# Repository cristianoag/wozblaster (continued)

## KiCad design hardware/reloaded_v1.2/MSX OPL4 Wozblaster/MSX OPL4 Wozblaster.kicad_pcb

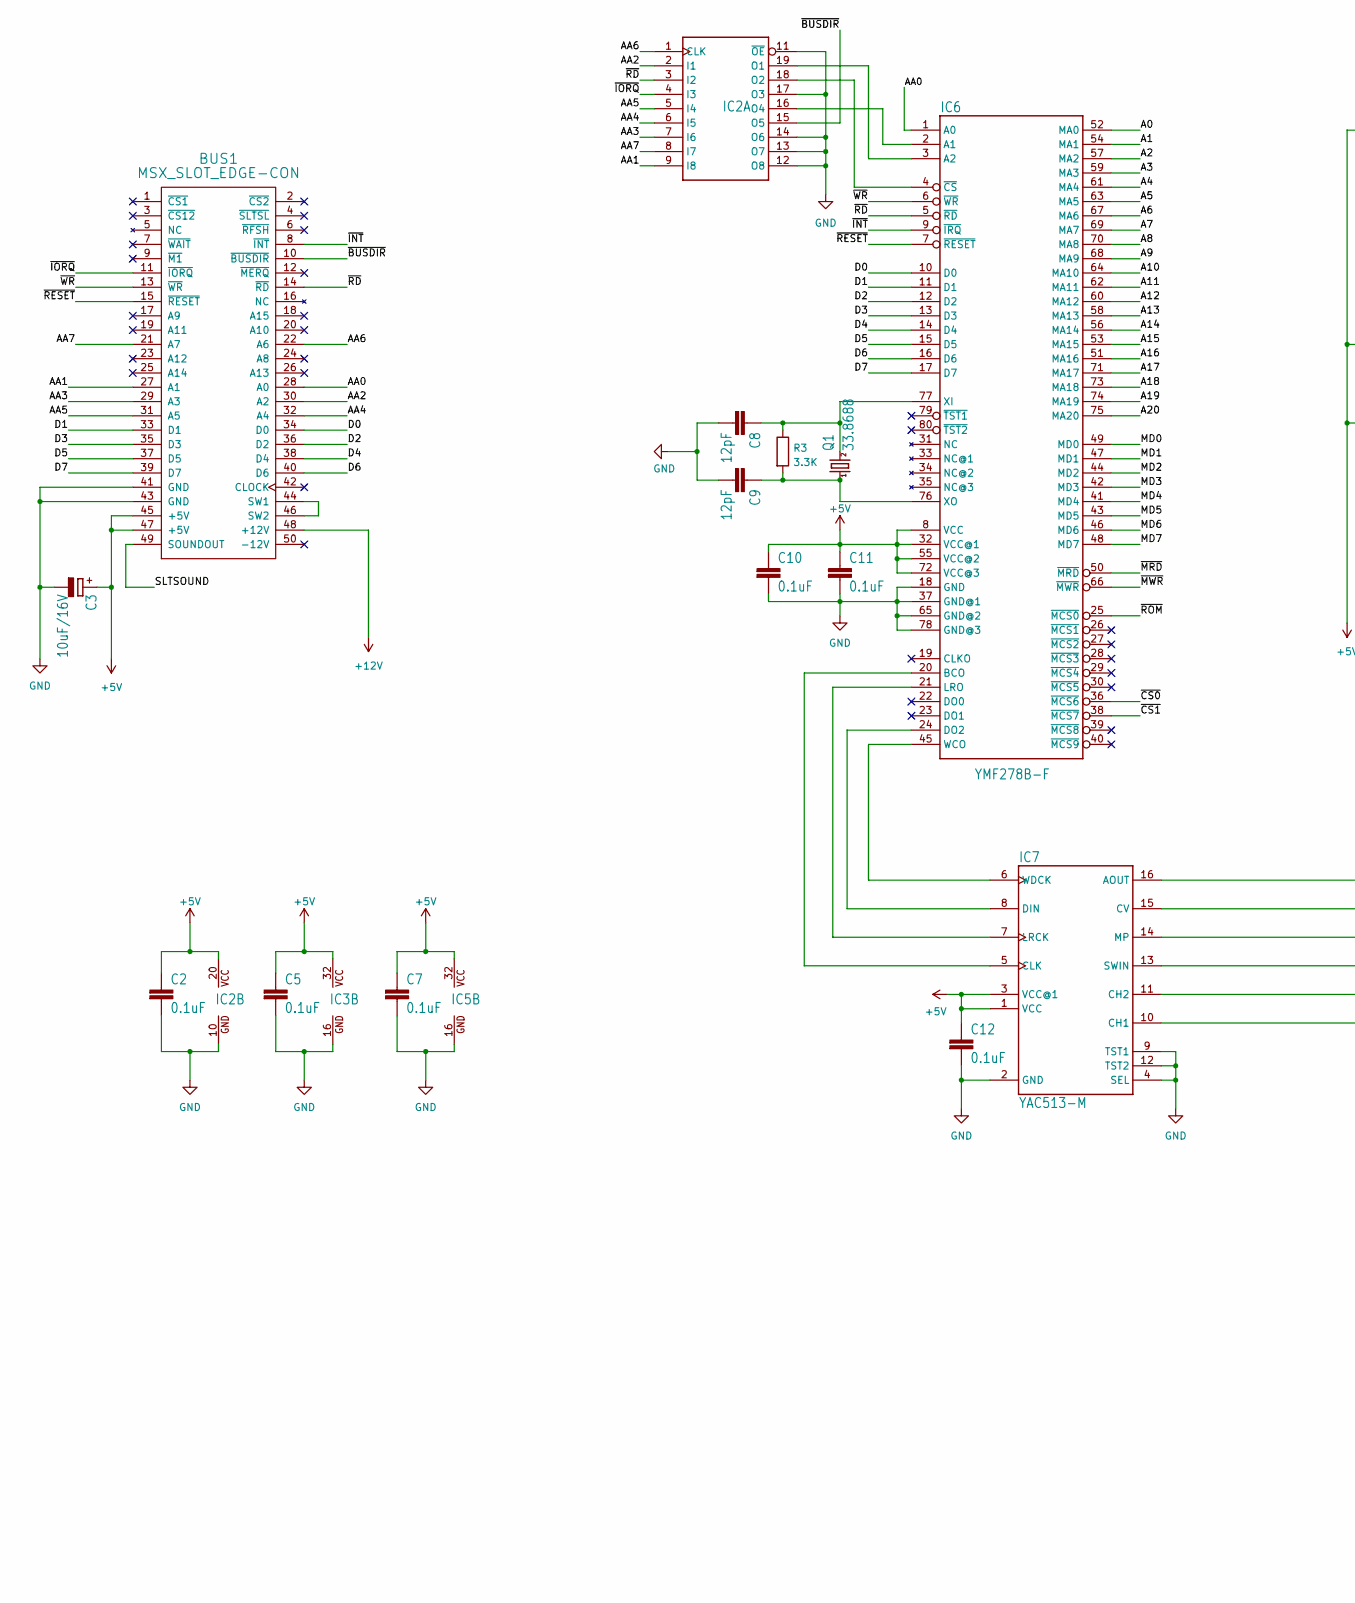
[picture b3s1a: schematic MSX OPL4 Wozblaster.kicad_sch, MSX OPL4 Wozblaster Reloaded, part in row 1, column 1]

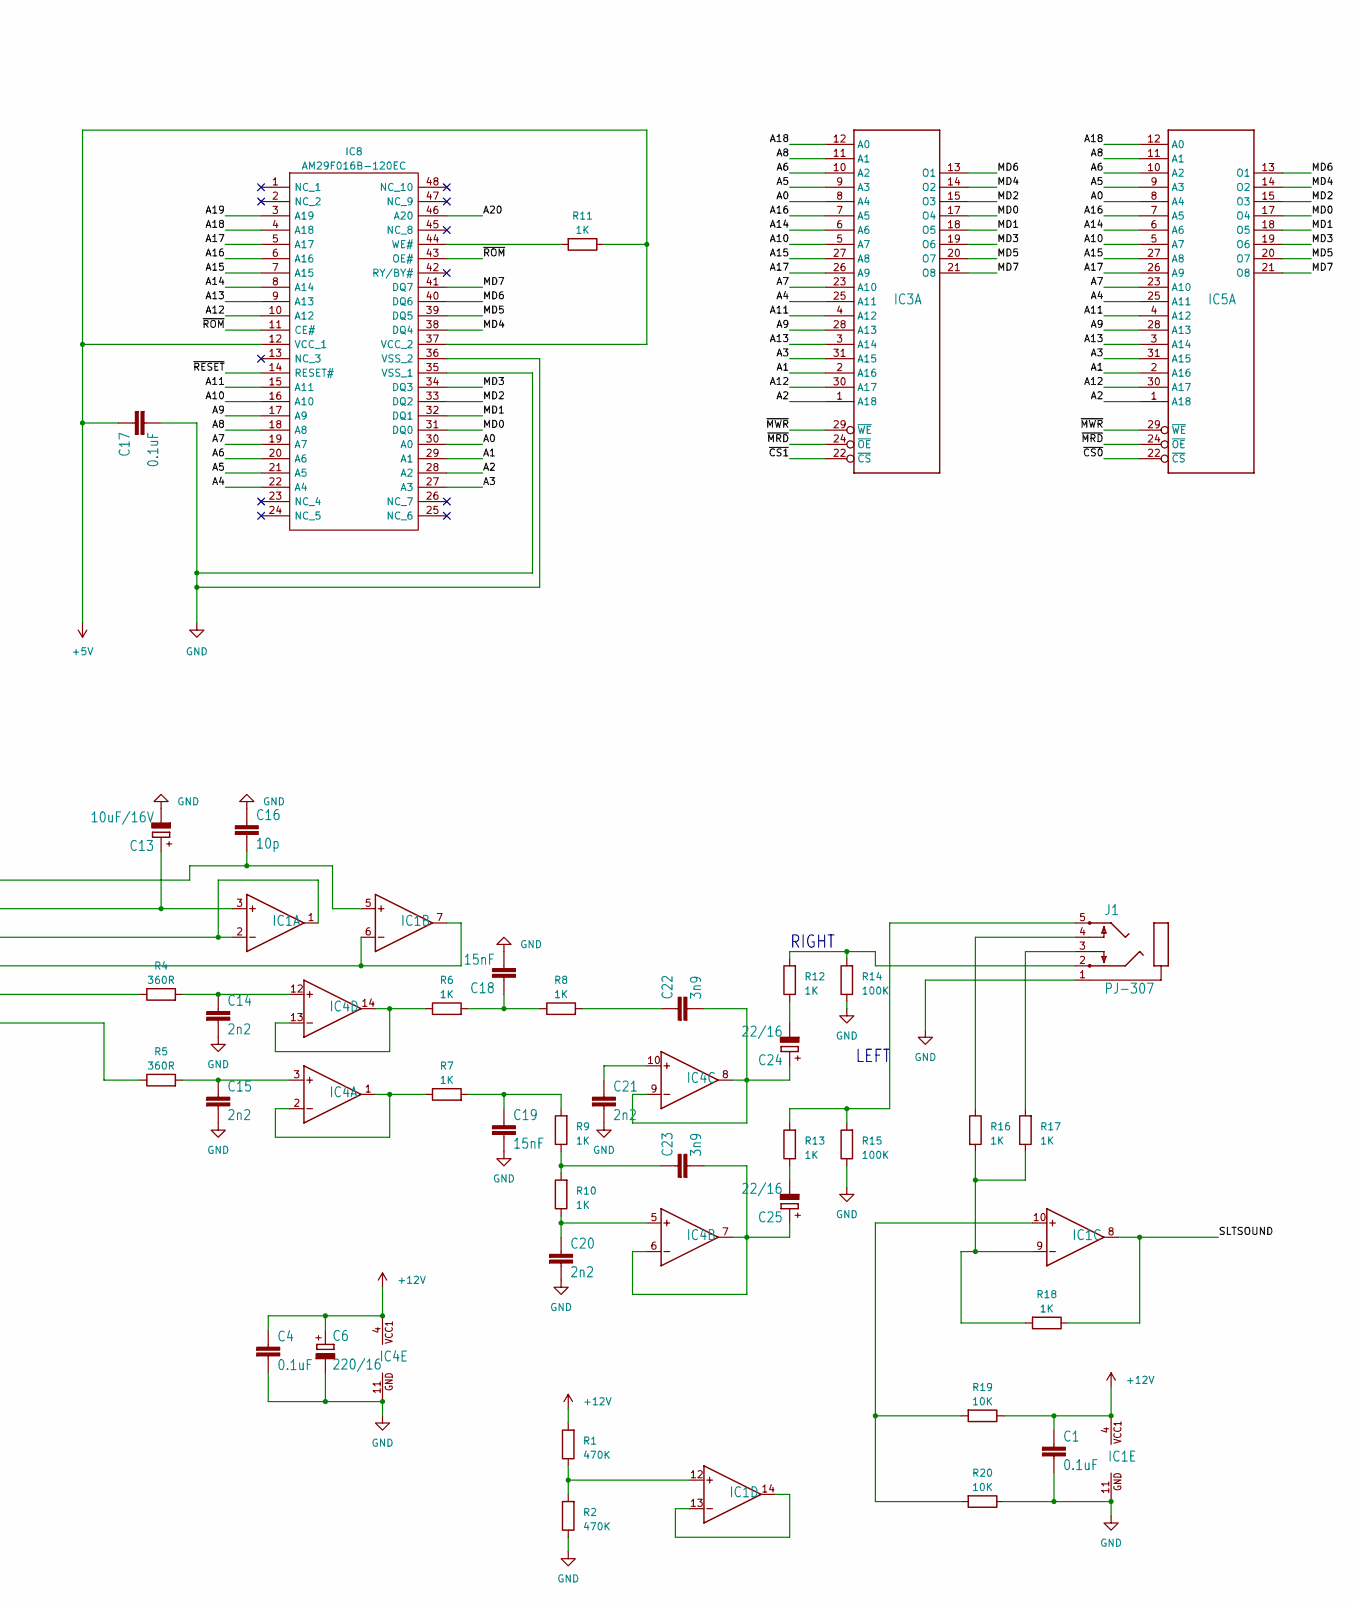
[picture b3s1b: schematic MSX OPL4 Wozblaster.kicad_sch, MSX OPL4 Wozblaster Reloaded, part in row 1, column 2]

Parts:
BUS1: MSX_SLOT_EDGE-CON; msx_cartridge; MPN n/a
C1, C2, C4, C5, C7, C10, C11, C12, C17: 0.1uF; C_0603_1608Metric
C3, C13: 10uF/16V; CP_EIA-3528-21_Kemet-B
C6: 220/16; CP_EIA-3528-21_Kemet-B
C8, C9: 12pF; C_0603_1608Metric
C14, C15, C20, C21: 2n2; C_0603_1608Metric
C16: 10p; C_0603_1608Metric
C18, C19: 15nF; C_0603_1608Metric
C22, C23: 3n9; C_0603_1608Metric
C24, C25: 22/16; CP_EIA-3528-21_Kemet-B
IC1, IC4: LF347; SO14-2
IC2: GAL16V8D; DIL20
IC3, IC5: KM684000ALG; SOP32L
IC6: YMF278B-F; 80-QFP
IC7: YAC513-M; 16SOP
IC8: AM29F016B-120EC; SOP50P2000X120-48N; Manufacturer_Part_Number AM29F016B-120EC
J1: PJ-307
Q1: 33.8688; Crystal_HC49-U_Vertical
R1, R2: 470K; R_0603_1608Metric
R3: 3.3K; R_0603_1608Metric
R4, R5: 360R; R_0603_1608Metric
R6, R7, R8, R9, R10, R11, R12, R13, R16, R17, R18: 1K; R_0603_1608Metric
R14, R15: 100K; R_0603_1608Metric
R19, R20: 10K; R_0603_1608Metric

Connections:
+5V: BUS1.45 (+5V), BUS1.47 (+5V), C2.1, C3.1 (+), C5.1, C7.1, C10.1, C11.1, C12.1, C17.1, IC2.20 (VCC), IC3.32 (VCC), IC5.32 (VCC), IC6.8 (VCC), IC6.32 (VCC@1), IC6.55 (VCC@2), IC6.72 (VCC@3), IC7.1 (VCC), IC7.3 (VCC@1), IC8.12 (VCC_1), IC8.37 (VCC_2), R11.1
+12V: BUS1.48 (+12V), C1.1, C4.1, C6.1 (+), IC1.4 (VCC), IC4.4 (VCC), R1.2, R19.1
/A0: IC3.8 (A4), IC5.8 (A4), IC6.52 (MA0), IC8.30 (A0)
/A1: IC3.2 (A16), IC5.2 (A16), IC6.54 (MA1), IC8.29 (A1)
/A2: IC3.1 (A18), IC5.1 (A18), IC6.57 (MA2), IC8.28 (A2)
/A3: IC3.31 (A15), IC5.31 (A15), IC6.59 (MA3), IC8.27 (A3)
/A4: IC3.25 (A11), IC5.25 (A11), IC6.61 (MA4), IC8.22 (A4)
/A5: IC3.9 (A3), IC5.9 (A3), IC6.63 (MA5), IC8.21 (A5)
/A6: IC3.10 (A2), IC5.10 (A2), IC6.67 (MA6), IC8.20 (A6)
/A7: IC3.23 (A10), IC5.23 (A10), IC6.69 (MA7), IC8.19 (A7)
/A8: IC3.11 (A1), IC5.11 (A1), IC6.70 (MA8), IC8.18 (A8)
/A9: IC3.28 (A13), IC5.28 (A13), IC6.68 (MA9), IC8.17 (A9)
/A10: IC3.5 (A7), IC5.5 (A7), IC6.64 (MA10), IC8.16 (A10)
/A11: IC3.4 (A12), IC5.4 (A12), IC6.62 (MA11), IC8.15 (A11)
/A12: IC3.30 (A17), IC5.30 (A17), IC6.60 (MA12), IC8.10 (A12)
/A13: IC3.3 (A14), IC5.3 (A14), IC6.58 (MA13), IC8.9 (A13)
/A14: IC3.6 (A6), IC5.6 (A6), IC6.56 (MA14), IC8.8 (A14)
/A15: IC3.27 (A8), IC5.27 (A8), IC6.53 (MA15), IC8.7 (A15)
/A16: IC3.7 (A5), IC5.7 (A5), IC6.51 (MA16), IC8.6 (A16)
/A17: IC3.26 (A9), IC5.26 (A9), IC6.71 (MA17), IC8.5 (A17)
/A18: IC3.12 (A0), IC5.12 (A0), IC6.73 (MA18), IC8.4 (A18)
/A19: IC6.74 (MA19), IC8.3 (A19)
/A20: IC6.75 (MA20), IC8.46 (A20)
/AA0: BUS1.28 (A0), IC6.1 (A0)
/AA1: BUS1.27 (A1), IC2.9 (I8)
/AA2: BUS1.30 (A2), IC2.2 (I1)
/AA3: BUS1.29 (A3), IC2.7 (I6)
/AA4: BUS1.32 (A4), IC2.6 (I5)
/AA5: BUS1.31 (A5), IC2.5 (I4)
/AA6: BUS1.22 (A6), IC2.1 (CLK)
/AA7: BUS1.21 (A7), IC2.8 (I7)
/D0: BUS1.34 (D0), IC6.10 (D0)
/D1: BUS1.33 (D1), IC6.11 (D1)
/D2: BUS1.36 (D2~), IC6.12 (D2)
/D3: BUS1.35 (D3), IC6.13 (D3)
/D4: BUS1.38 (D4), IC6.14 (D4)
/D5: BUS1.37 (D5), IC6.15 (D5)
/D6: BUS1.40 (D6), IC6.16 (D6)
/D7: BUS1.39 (D7), IC6.17 (D7)
/MD0: IC3.17 (O4), IC5.17 (O4), IC6.49 (MD0), IC8.31 (DQ0)
/MD1: IC3.18 (O5), IC5.18 (O5), IC6.47 (MD1), IC8.32 (DQ1)
/MD2: IC3.15 (O3), IC5.15 (O3), IC6.44 (MD2), IC8.33 (DQ2)
/MD3: IC3.19 (O6), IC5.19 (O6), IC6.42 (MD3), IC8.34 (DQ3)
/MD4: IC3.14 (O2), IC5.14 (O2), IC6.41 (MD4), IC8.38 (DQ4)
/MD5: IC3.20 (O7), IC5.20 (O7), IC6.43 (MD5), IC8.39 (DQ5)
/MD6: IC3.13 (O1), IC5.13 (O1), IC6.46 (MD6), IC8.40 (DQ6)
/MD7: IC3.21 (O8), IC5.21 (O8), IC6.48 (MD7), IC8.41 (DQ7)
/SLTSOUND: BUS1.49 (SOUNDOUT), IC1.8 (OUT), R18.1
/~BUSDIR: BUS1.10 (~BUSDIR), IC2.15 (O5)
/~CS0: IC5.22 (~CS), IC6.36 (~MCS6)
/~CS1: IC3.22 (~CS), IC6.38 (~MCS7)
/~INT: BUS1.8 (~INT), IC6.9 (~IRQ)
/~IORQ: BUS1.11 (~IORQ), IC2.4 (I3)
/~MRD: IC3.24 (~OE), IC5.24 (~OE), IC6.50 (~MRD)
/~MWR: IC3.29 (~WE), IC5.29 (~WE), IC6.66 (~MWR)
/~RD: BUS1.14 (~RD), IC2.3 (I2), IC6.5 (~RD)
/~RESET: BUS1.15 (~RESET), IC6.7 (~RESET), IC8.14 (RESET#)
/~ROM: IC6.25 (~MCS0), IC8.11 (CE#), IC8.43 (OE#)
/~WR: BUS1.13 (~WR), IC6.6 (~WR)
GND: BUS1.41 (GND), BUS1.43 (GND), C1.2, C2.2, C3.2 (-), C4.2, C5.2, C6.2 (-), C7.2, C8.2, C9.2, C10.2, C11.2, C12.2, C13.2 (-), C14.2, C15.2, C16.1, C17.2, C18.2, C19.2, C20.2, C21.2, IC1.11 (GND), IC2.10 (GND), IC2.11 (~OE), IC2.12 (O8), IC2.13 (O7), IC2.14 (O6), IC2.17 (O3), IC3.16 (GND), IC4.11 (GND), IC5.16 (GND), IC6.18 (GND), IC6.37 (GND@1), IC6.65 (GND@2), IC6.78 (GND@3), IC7.2 (GND), IC7.4 (SEL), IC7.9 (TST1), IC7.12 (TST2), IC8.35 (VSS_1), IC8.36 (VSS_2), J1.1, R2.1, R14.1, R15.1, R20.1
unnamed: BUS1.44 (SW1), BUS1.46 (SW2)
unnamed: C13.1 (+), IC1.3 (IN+), IC7.15 (CV)
unnamed: C18.1, R6.2, R8.1
unnamed: C19.1, R7.2, R9.2
unnamed: C22.1, R8.2
unnamed: C23.1, R9.1, R10.2
unnamed: C22.2, C24.1 (+), IC4.8 (OUT), IC4.9 (IN-)
unnamed: C24.2 (-), R12.1
unnamed: C23.2, C25.1 (+), IC4.6 (IN-), IC4.7 (OUT)
unnamed: C25.2 (-), R13.1
unnamed: IC1.1 (OUT), IC1.2 (IN-), IC7.14 (MP)
unnamed: C16.2, IC1.5 (IN+), IC7.16 (AOUT)
unnamed: IC1.6 (IN-), IC1.7 (OUT), IC7.13 (SWIN)
unnamed: IC1.10 (IN+), R19.2, R20.2
unnamed: IC1.9 (IN-), R16.2, R17.1, R18.2
unnamed: IC1.12 (IN+), R1.1, R2.2
unnamed: IC1.13 (IN-), IC1.14 (OUT)
unnamed: IC2.19 (O1), IC6.3 (A2)
unnamed: IC2.18 (O2), IC6.4 (~CS)
unnamed: IC2.16 (O4), IC6.2 (A1)
unnamed: C15.1, IC4.3 (IN+), R5.2
unnamed: IC4.1 (OUT), IC4.2 (IN-), R7.1
unnamed: C20.1, IC4.5 (IN+), R10.1
unnamed: C21.1, IC4.10 (IN+)
unnamed: C14.1, IC4.12 (IN+), R4.2
unnamed: IC4.13 (IN-), IC4.14 (OUT), R6.1
unnamed: IC6.20 (BCO), IC7.5 (CLK)
unnamed: IC6.24 (DO2), IC7.8 (DIN)
unnamed: IC6.21 (LRO), IC7.7 (LRCK)
unnamed: IC6.45 (WCO), IC7.6 (WDCK)
unnamed: C8.1, IC6.77 (XI), Q1.2, R3.1
unnamed: C9.1, IC6.76 (XO), Q1.1, R3.2
unnamed: IC7.10 (CH1), R5.1
unnamed: IC7.11 (CH2), R4.1
unnamed: IC8.44 (WE#), R11.2
unnamed: J1.2, R12.2, R14.2
unnamed: J1.3, R17.2
unnamed: J1.4, R16.1
unnamed: J1.5, R13.2, R15.2

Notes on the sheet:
RIGHT
LEFT

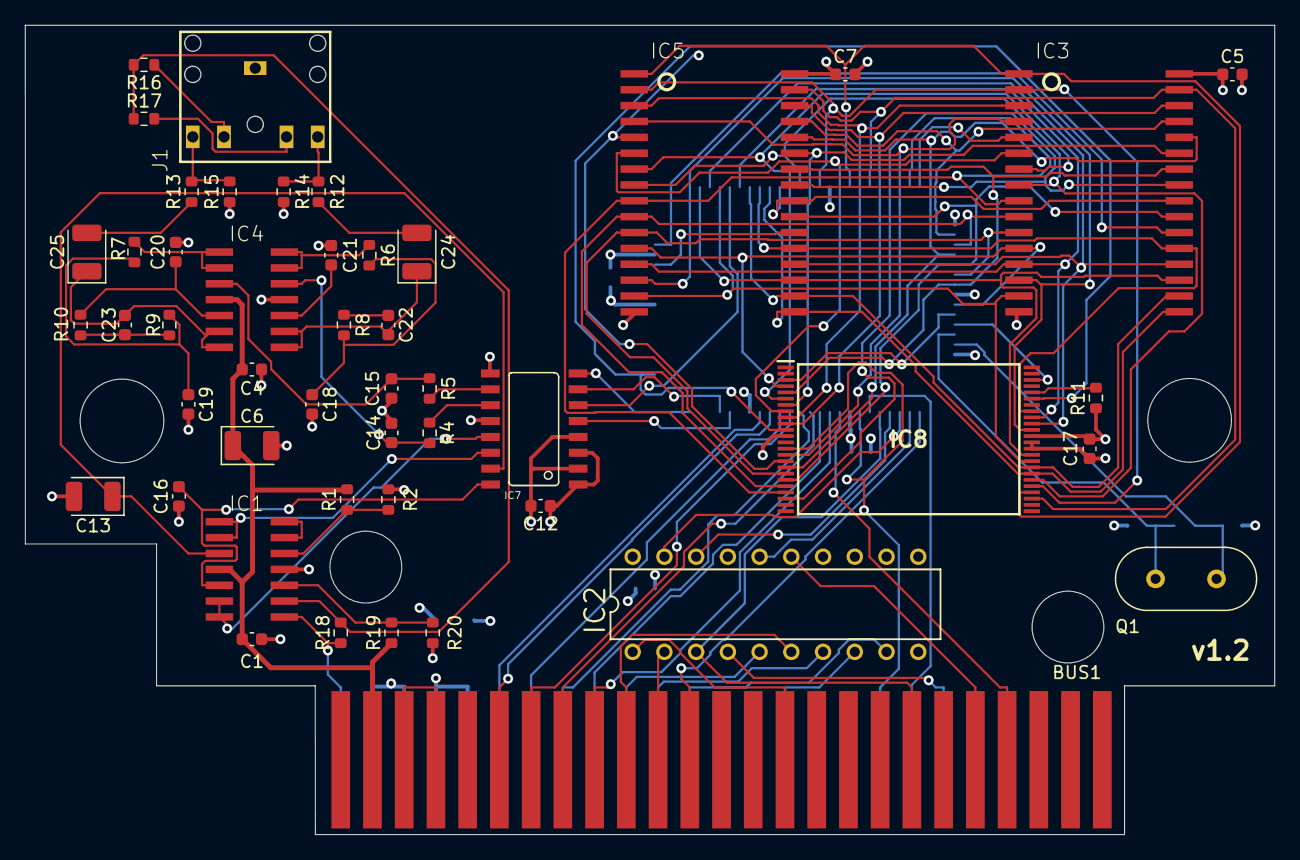
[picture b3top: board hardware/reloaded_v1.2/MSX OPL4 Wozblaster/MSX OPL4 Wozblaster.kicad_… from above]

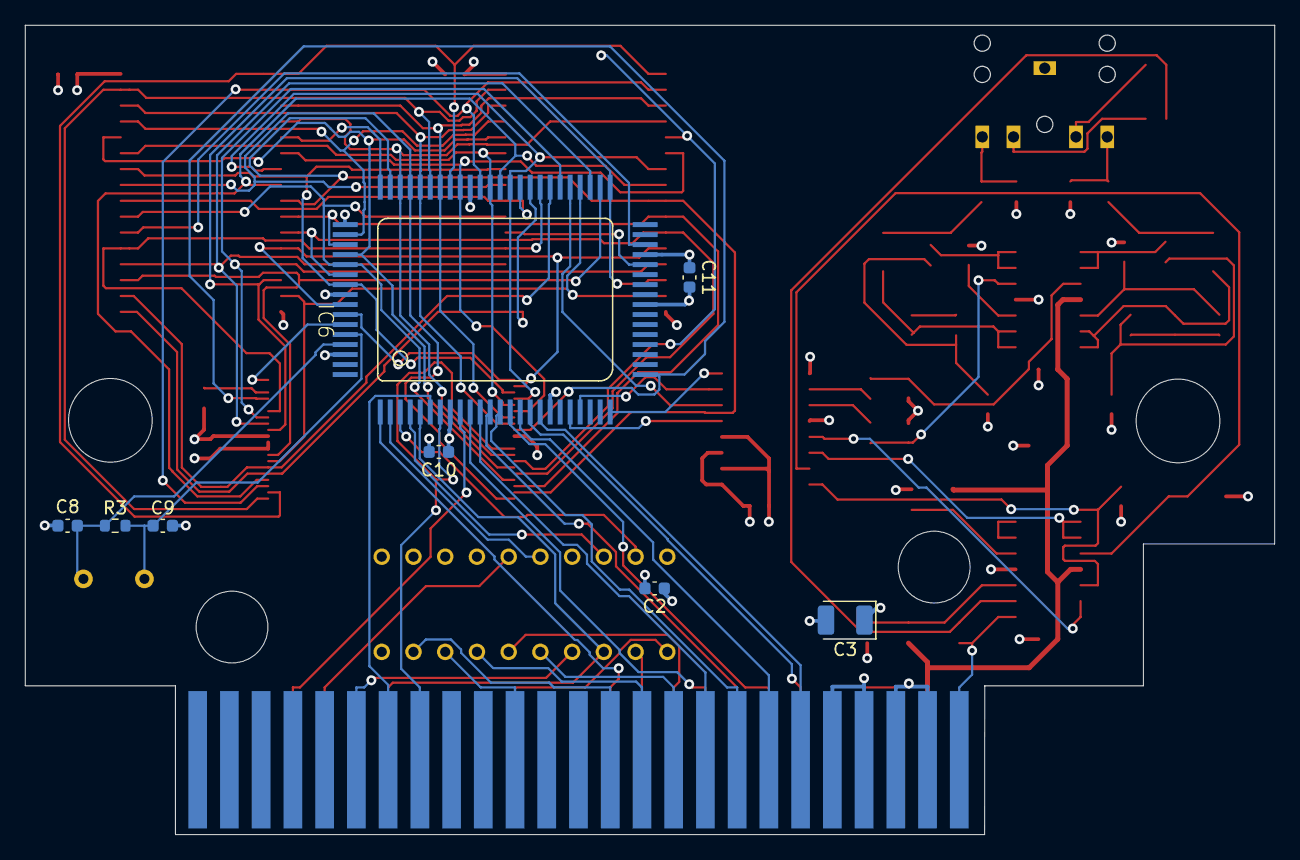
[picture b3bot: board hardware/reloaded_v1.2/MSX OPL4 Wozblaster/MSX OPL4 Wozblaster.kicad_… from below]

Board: 4 copper layers, 100.0 x 64.8 mm, 56 parts (8 on the bottom side), 99 nets.

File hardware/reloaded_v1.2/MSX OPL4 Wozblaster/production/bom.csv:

Designator,Footprint,Quantity,Value,LCSC Part #
C1,0603,1,0.1uF,
C10,0603,1,0.1uF,
C11,0603,1,0.1uF,
C12,0603,1,0.1uF,
"C13, C3",CP_EIA-3528-21_Kemet-B,2,10uF/16V,
C14,0603,1,2n2,
C15,0603,1,2n2,
C16,0603,1,10p,
C17,0603,1,0.1uF,
C18,0603,1,15nF,
C19,0603,1,15nF,
C2,0603,1,0.1uF,
C20,0603,1,2n2,
C21,0603,1,2n2,
C22,0603,1,3n9,
C23,0603,1,3n9,
"C24, C25",CP_EIA-3528-21_Kemet-B,2,22/16,
C4,0603,1,0.1uF,
C5,0603,1,0.1uF,
C6,CP_EIA-3528-21_Kemet-B,1,220/16,
C7,0603,1,0.1uF,
C8,0603,1,12pF,
C9,0603,1,12pF,
"IC1, IC4",SO14-2,2,LF347,
IC2,DIL20,1,GAL16V8D,
"IC3, IC5",SOP32L,2,KM684000ALG,
IC6,80-QFP,1,YMF278B-F,
IC7,16SOP,1,YAC513-M,
IC8,SOP50P2000X120-48N,1,AM29F016B-120EC,
J1,PJ-307,1,PJ-307,
Q1,Crystal_HC49-U_Vertical,1,33.8688,
R1,0603,1,470K,
R10,0603,1,1K,
R11,0603,1,1K,
R12,0603,1,1K,
R13,0603,1,1K,
R14,0603,1,100K,
R15,0603,1,100K,
R16,0603,1,1K,
R17,0603,1,1K,
R18,0603,1,1K,
R19,0603,1,10K,
R2,0603,1,470K,
R20,0603,1,10K,
R3,0603,1,3.3K,
R4,0603,1,360R,
R5,0603,1,360R,
R6,0603,1,1K,
R7,0603,1,1K,
R8,0603,1,1K,
R9,0603,1,1K,

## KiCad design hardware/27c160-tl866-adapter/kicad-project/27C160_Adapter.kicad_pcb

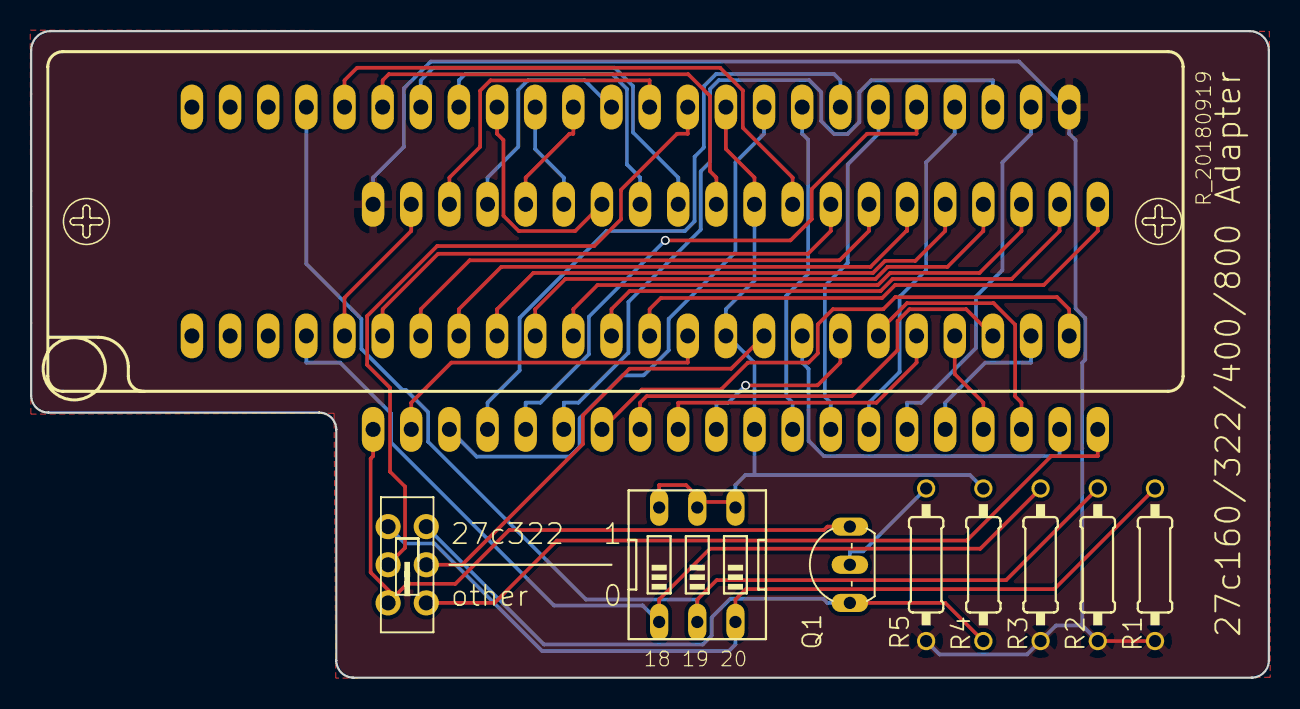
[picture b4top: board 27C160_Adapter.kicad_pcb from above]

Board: 2 copper layers, 82.4 x 43.1 mm, 12 parts (0 on the bottom side), 46 nets.

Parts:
G001: LOGO; mini-mods
Q1: BC327; TO92-EBC
R1, R2, R3, R4, R5: 10k; 0207%2f10
REF01: OSHW-Logo2_9.8x8mm_SilkScreen
SW1: MS22D16
SW2: DIP; EDG-03
U1: 27C4002
ZX1: 3M_248-3345

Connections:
/A0: U1.21, ZX1.13
/A1: U1.22, ZX1.12
/A2: U1.23, ZX1.11
/A3: U1.24, ZX1.10
/A4: U1.25, ZX1.9
/A5: U1.26, ZX1.8
/A6: U1.27, ZX1.7
/A7: U1.28, ZX1.6
/A8: U1.29, ZX1.44
/A9: U1.31, ZX1.43
/A10: U1.32, ZX1.42
/A11: U1.33, ZX1.41
/A12: U1.34, ZX1.40
/A13: U1.35, ZX1.39
/A14: U1.36, ZX1.38
/A15: U1.37, ZX1.37
/A16: U1.38, ZX1.36
/A17: U1.39, ZX1.5
/A18: R3.1, SW2.1, ZX1.4
/A19: R2.1, SW2.2, ZX1.45
/A20: R1.1, SW1.3, SW2.3
/D0: U1.19, ZX1.17
/D1: U1.18, ZX1.19
/D2: U1.17, ZX1.21
/D3: U1.16, ZX1.23
/D4: U1.15, ZX1.26
/D5: U1.14, ZX1.28
/D6: U1.13, ZX1.30
/D7: U1.12, ZX1.32
/D8: U1.10, ZX1.18
/D9: U1.9, ZX1.20
/D10: U1.8, ZX1.22
/D11: U1.7, ZX1.24
/D12: U1.6, ZX1.27
/D13: U1.5, ZX1.29
/D14: U1.4, ZX1.31
/D15: U1.3, ZX1.33
/E: U1.2, ZX1.14
/N$1: Q1.B, R5.2
/N$2: SW1.2, ZX1.35
/N$4: Q1.C, R4.2, SW1.6
/N$5: SW1.4, U1.20
/N$6: SW1.5, ZX1.16
/VPP: Q1.E, SW1.1, U1.1
GND: R4.1, SW2.4, SW2.5, SW2.6, U1.11, U1.30, ZX1.15, ZX1.34
VCC: R1.2, R2.2, R3.2, R5.1, U1.40, ZX1.25

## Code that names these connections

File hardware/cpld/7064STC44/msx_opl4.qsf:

# -------------------------------------------------------------------------- #
#
# Copyright (C) 1991-2011 Altera Corporation
# Your use of Altera Corporation's design tools, logic functions 
# and other software and tools, and its AMPP partner logic 
# functions, and any output files from any of the foregoing 
# (including device programming or simulation files), and any 
# associated documentation or information are expressly subject 
# to the terms and conditions of the Altera Program License 
# Subscription Agreement, Altera MegaCore Function License 
# Agreement, or other applicable license agreement, including, 
# without limitation, that your use is for the sole purpose of 
# programming logic devices manufactured by Altera and sold by 
# Altera or its authorized distributors.  Please refer to the 
# applicable agreement for further details.
#
# -------------------------------------------------------------------------- #
#
# Quartus II
# Version 11.0 Build 208 07/03/2011 Service Pack 1 SJ Web Edition
# Date created = 17:33:55  November 16, 2024
#
# -------------------------------------------------------------------------- #
#
# Notes:
#
# 1) The default values for assignments are stored in the file:
#		msx_opl4_assignment_defaults.qdf
#    If this file doesn't exist, see file:
#		assignment_defaults.qdf
#
# 2) Altera recommends that you do not modify this file. This
#    file is updated automatically by the Quartus II software
#    and any changes you make may be lost or overwritten.
#
# -------------------------------------------------------------------------- #


set_global_assignment -name FAMILY MAX7000S
set_global_assignment -name DEVICE "EPM7064STC44-10"
set_global_assignment -name TOP_LEVEL_ENTITY msx_opl4
set_global_assignment -name ORIGINAL_QUARTUS_VERSION "11.0 SP1"
set_global_assignment -name PROJECT_CREATION_TIME_DATE "17:33:55  NOVEMBER 16, 2024"
set_global_assignment -name LAST_QUARTUS_VERSION "11.0 SP1"
set_global_assignment -name ERROR_CHECK_FREQUENCY_DIVISOR "-1"
set_global_assignment -name MIN_CORE_JUNCTION_TEMP 0
set_global_assignment -name MAX_CORE_JUNCTION_TEMP 85
set_global_assignment -name VERILOG_FILE msx_opl4.v
set_global_assignment -name MAX7000_DEVICE_IO_STANDARD TTL
set_location_assignment PIN_26 -to TCK
set_location_assignment PIN_1 -to TDI
set_location_assignment PIN_32 -to TDO
set_location_assignment PIN_7 -to TMS
set_location_assignment PIN_18 -to msx_A1
set_location_assignment PIN_19 -to msx_A2
set_location_assignment PIN_20 -to msx_A3
set_location_assignment PIN_21 -to msx_A4
set_location_assignment PIN_22 -to msx_A5
set_location_assignment PIN_14 -to msx_A6
set_location_assignment PIN_15 -to msx_A7
set_location_assignment PIN_12 -to msx_IORQ
set_location_assignment PIN_13 -to msx_RD
set_location_assignment PIN_11 -to msx_busdir
set_location_assignment PIN_6 -to y_A1
set_location_assignment PIN_5 -to y_A2
set_location_assignment PIN_8 -to y_CS

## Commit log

2023-01-01 initial load
2023-01-01 images and labels
2023-01-01 hardware folder
2023-01-01 adapter to program the eprom
2023-01-01 software
2023-01-02 fixes to the PCB
2023-01-02 save project kicad
2023-01-02 soundin version
2023-01-02 removing backups
2023-01-02 case for the wozblaster v1
2023-01-02 fixes
2023-01-03 iteractions of the case
2023-01-04 Additional Images and labels
2023-01-09 fixing images
2023-01-10 JED fix
2023-01-20 conversion fixes
2023-02-20 v1.2 and v2 work in progress
2023-02-20 Readme Updates
2023-02-20 Hardware Readme
2023-02-20 Readme adjustments
2023-02-20 Text Improvements
2023-02-20 PCB image
2023-02-20 Uploading Gerbers vor v1.2
2023-03-22 v3 and multiple adjusts
2023-04-21 Reloaded 3.1
2023-04-21 minor changes to README
2023-04-21 footprints for 3.1
2023-04-21 Update video on the description
2023-05-16 v3.2
2023-06-06 v3.3 update
2023-06-06 footprint adjustments
2023-08-27 v4.0 upload and README adjustments
2023-09-24 Footprint adjustments, README, small fixes
2023-09-26 gerbers
2024-03-10 License
2024-03-10 README update
2024-03-10 README
2024-03-14 Update images
2024-10-13 v5.0 initial upload
2024-11-16 new verilog selection code. readme adjustments for v5
2024-11-17 verilog code for v5
2024-11-17 datasheets and readme update
2024-11-18 cpld code and pcb adjustments after tests
2024-11-19 7032 cpld files
2024-11-19 ibom update
2024-11-19 readme.md update
2026-02-14 New version 4.6. New CPLD code to solve issues with TurboR
